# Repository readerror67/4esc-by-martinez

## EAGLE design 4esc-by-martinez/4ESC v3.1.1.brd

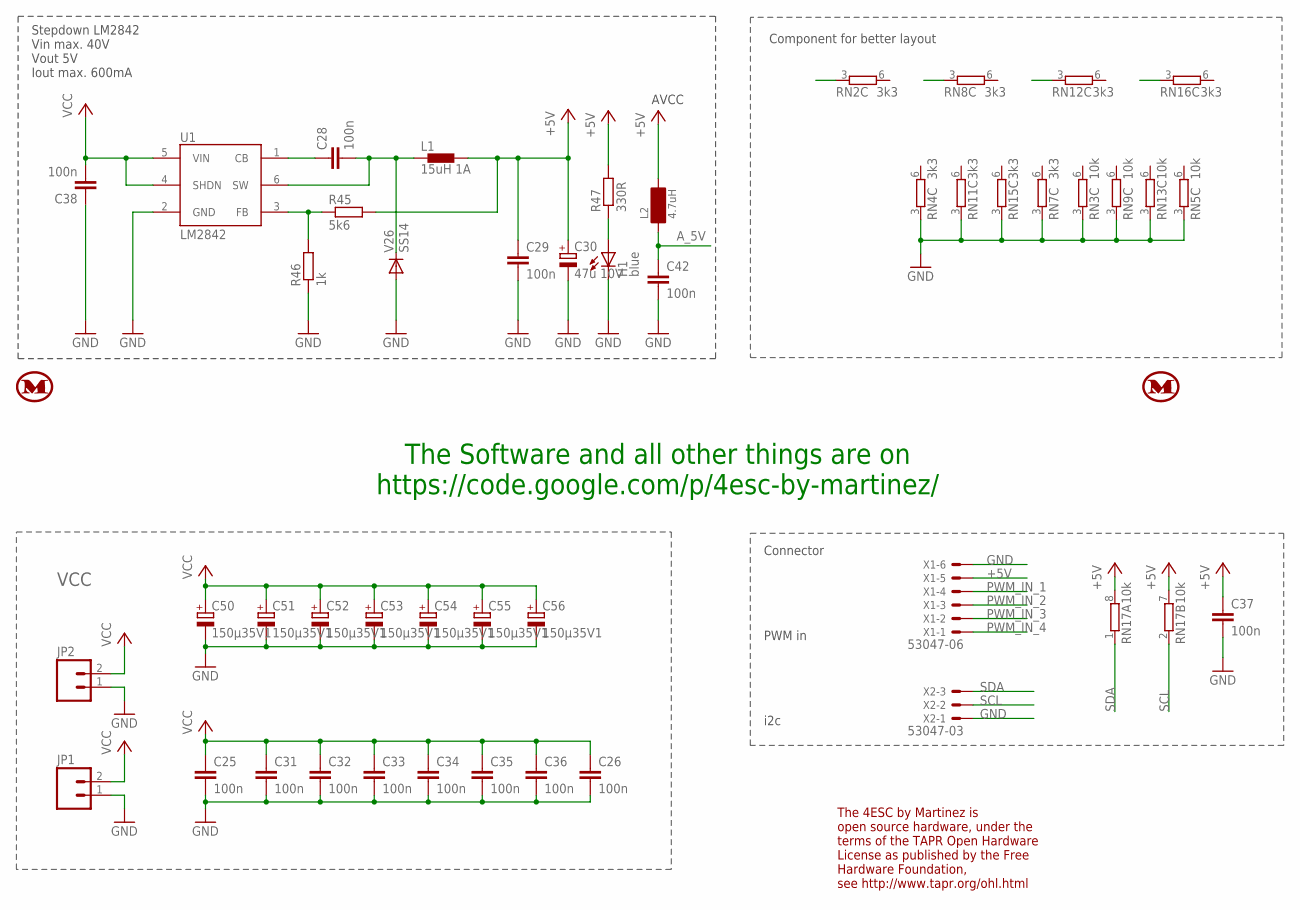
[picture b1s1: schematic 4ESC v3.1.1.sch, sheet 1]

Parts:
C25, C26, C28, C29, C31, C32, C33, C34, C35, C36, C37, C42: 100n; C0603K
C30: 47u 10V; C/6032-28R
C38: 100n; C1206
C50, C51, C52, C53, C54, C55, C56: 150µ35V1; ELKO_MARTINEZ
H1: blue; CHIPLED_0603
JP1, JP2: M021X02_NO_SILK; 1X02_NO_SILK
L1: 15uH 1A; CDRH4D28
L2: 4.7uH; L0805
R45: 5k6; R0603
R46: 1k; R0603
R47: 330R; R0603
RN2, RN4, RN7, RN8, RN11, RN12, RN15, RN16: 3k3; 4X0402ARV341
RN3, RN5, RN9, RN13, RN17: 10k; 4X0402ARV341
U1: LM2842; SOT23-6
U$1, U$2: M
U$3, U$4: 4ESC_05MM; 4ESC_05MM_HOCH
V26: SS14; DO214AC
X1: 53047-06
X2: 53047-03

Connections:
+5V: C29.1, C30.+, C37.1, L1.P$2 (2), L2.2, R45.2, R47.2, RN17.7 (2), RN17.8 (2), X1.5; also elsewhere on the board
A_5V: C42.1, L2.1; also elsewhere on the board
GND: C25.2, C26.2, C29.2, C30.-, C31.2, C32.2, C33.2, C34.2, C35.2, C36.2, C37.2, C38.1, C42.2, C50.-, C50.-1 (-), C51.-, C51.-1 (-), C52.-, C52.-1 (-), C53.-, C53.-1 (-), C54.-, C54.-1 (-), C55.-, C55.-1 (-), C56.-, C56.-1 (-), H1.C, JP1.1, JP2.1, R46.1, RN3.3 (1), RN4.3 (1), RN5.3 (1), RN7.3 (1), RN9.3 (1), RN11.3 (1), RN13.3 (1), RN15.3 (1), U1.2 (GND), V26.A, X1.6, X2.1; also elsewhere on the board
unnamed: C28.2, L1.P$1 (1), U1.6 (SW), V26.C
unnamed: C28.1, U1.1 (CB)
unnamed: R45.1, R46.2, U1.3 (FB)
unnamed: H1.A, R47.1
PWM_IN_1: X1.4; also elsewhere on the board
PWM_IN_2: X1.3; also elsewhere on the board
PWM_IN_3: X1.2; also elsewhere on the board
PWM_IN_4: X1.1; also elsewhere on the board
SCL: RN17.2 (1), X2.2; also elsewhere on the board
SDA: RN17.1, X2.3; also elsewhere on the board
SENSE_STAR_1: RN2.3 (1); also elsewhere on the board
SENSE_STAR_2: RN8.3 (1); also elsewhere on the board
SENSE_STAR_3: RN12.3 (1); also elsewhere on the board
SENSE_STAR_4: RN16.3 (1); also elsewhere on the board
VCC: C25.1, C26.1, C31.1, C32.1, C33.1, C34.1, C35.1, C36.1, C38.2, C50.+, C50.+1 (+), C51.+, C51.+1 (+), C52.+, C52.+1 (+), C53.+, C53.+1 (+), C54.+, C54.+1 (+), C55.+, C55.+1 (+), C56.+, C56.+1 (+), JP1.2, JP2.2, U1.4 (SHDN), U1.5 (VIN); also elsewhere on the board

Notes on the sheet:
VCC
Stepdown LM2842 Vin max. 40V Vout 5V Iout max. 600mA
Connector PWM in i2c
Component for better layout
AVCC
The 4ESC by Martinez is open source hardware, under the terms of the TAPR Open Hardware License as published by the Free Hardware Foundation, see http://www.tapr.org/ohl.html
The Software and all other things are on https://code.google.com/p/4esc-by-martinez/

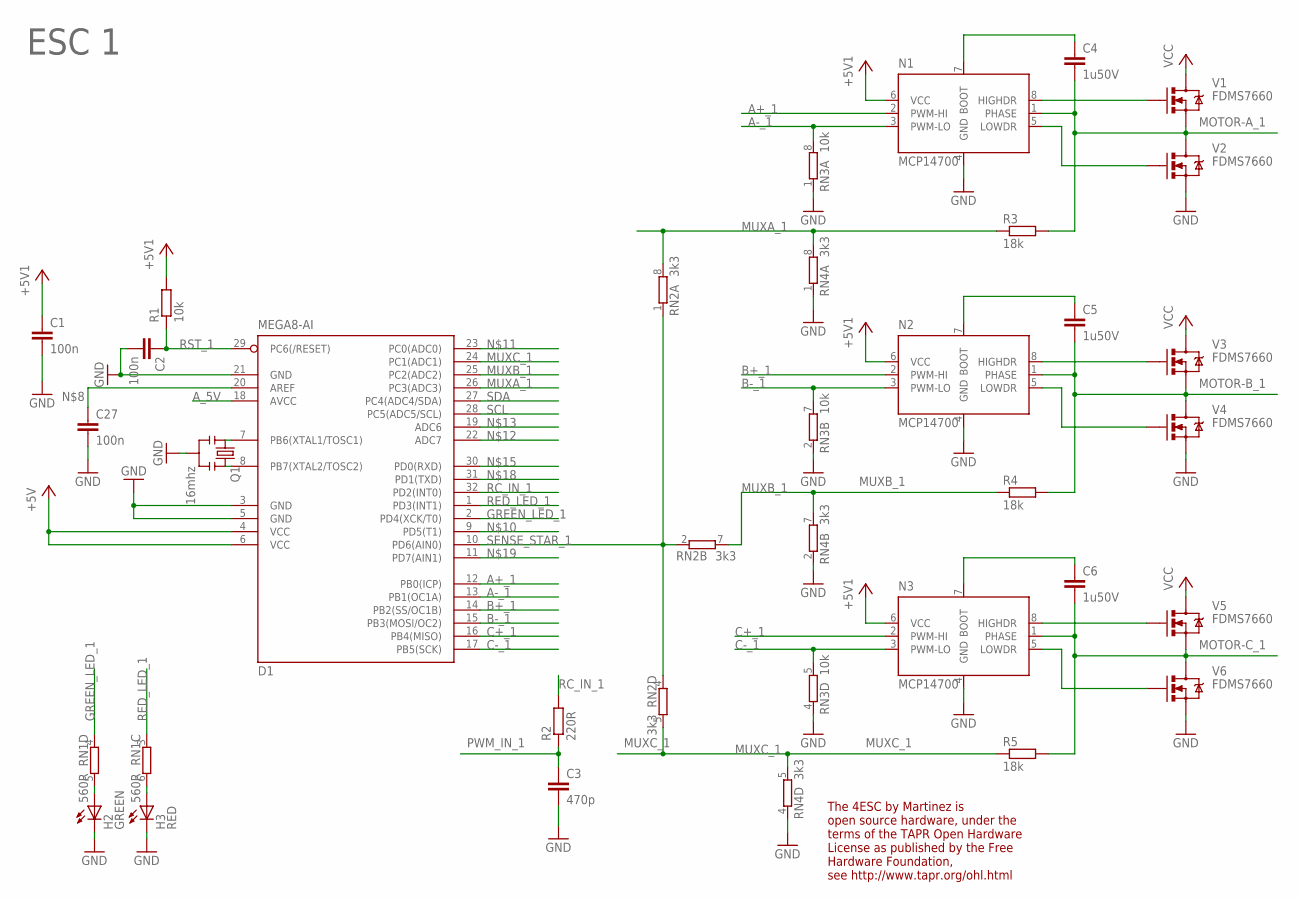
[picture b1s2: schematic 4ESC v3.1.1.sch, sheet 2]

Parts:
C1, C2, C27: 100n; C0603K
C3: 470p; C0603K
C4, C5, C6: 1u50V; C0805K
D1: MEGA8-AI; TQFP32-08
H2: GREEN; CHIPLED_0603
H3: RED; CHIPLED_0603
N1, N2, N3: MCP14700; DFN3X3P8
Q1: 16mhz; RESONATOR-SMD
R1: 10k; R0603
R2: 220R; R0603
R3, R4, R5: 18k; R0603
RN1: 560R; 4X0402ARV341
RN2, RN4: 3k3; 4X0402ARV341
RN3: 10k; 4X0402ARV341
V1, V2, V3, V4, V5, V6: FDMS7660; POWER56

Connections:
+5V: C1.1, D1.4 (VCC), D1.6 (VCC), N1.6 (VCC), N2.6 (VCC), N3.6 (VCC), R1.2; also elsewhere on the board
A+_1: D1.12 (PB0(ICP)), N1.2 (PWM-HI)
A-_1: D1.13 (PB1(OC1A)), N1.3 (PWM-LO), RN3.8 (2)
A_5V: D1.18 (AVCC); also elsewhere on the board
B+_1: D1.14 (PB2(SS/OC1B)), N2.2 (PWM-HI)
B-_1: D1.15 (PB3(MOSI/OC2)), N2.3 (PWM-LO), RN3.7 (2)
C+_1: D1.16 (PB4(MISO)), N3.2 (PWM-HI)
C-_1: D1.17 (PB5(SCK)), N3.3 (PWM-LO), RN3.5 (2)
GND: C1.2, C2.2, C3.2, C27.2, D1.3 (GND), D1.5 (GND), D1.21 (GND), H2.C, H3.C, N1.4 (GND), N2.4 (GND), N3.4 (GND), Q1.2, RN3.1, RN3.2 (1), RN3.4 (1), RN4.1, RN4.2 (1), RN4.4 (1), V2.P$1 (S), V2.P$2 (S), V2.P$3 (S), V4.P$1 (S), V4.P$2 (S), V4.P$3 (S), V6.P$1 (S), V6.P$2 (S), V6.P$3 (S); also elsewhere on the board
GREEN_LED_1: D1.2 (PD4(XCK/T0)), RN1.4 (1)
MOTOR-A_1: C4.2, N1.1 (PHASE), R3.2, V1.P$1 (S), V1.P$2 (S), V1.P$3 (S), V2.P$5 (D), V2.P$6 (D), V2.P$7 (D), V2.P$8 (D), V2.P$9 (D)
MOTOR-B_1: C5.2, N2.1 (PHASE), R4.2, V3.P$1 (S), V3.P$2 (S), V3.P$3 (S), V4.P$5 (D), V4.P$6 (D), V4.P$7 (D), V4.P$8 (D), V4.P$9 (D)
MOTOR-C_1: C6.2, N3.1 (PHASE), R5.2, V5.P$1 (S), V5.P$2 (S), V5.P$3 (S), V6.P$5 (D), V6.P$6 (D), V6.P$7 (D), V6.P$8 (D), V6.P$9 (D)
MUXA_1: D1.26 (PC3(ADC3)), R3.1, RN2.8 (2), RN4.8 (2)
MUXB_1: D1.25 (PC2(ADC2)), R4.1, RN2.7 (2), RN4.7 (2)
MUXC_1: D1.24 (PC1(ADC1)), R5.1, RN2.5 (2), RN4.5 (2)
unnamed: N1.5 (LOWDR), V2.P$4 (G)
unnamed: N2.5 (LOWDR), V4.P$4 (G)
unnamed: D1.8 (PB7(XTAL2/TOSC2)), Q1.3
unnamed: N3.5 (LOWDR), V6.P$4 (G)
unnamed: D1.7 (PB6(XTAL1/TOSC1)), Q1.1
unnamed: H3.A, RN1.6 (2)
unnamed: H2.A, RN1.5 (2)
unnamed: C27.1, D1.20 (AREF)
unnamed: N1.8 (HIGHDR), V1.P$4 (G)
unnamed: N2.8 (HIGHDR), V3.P$4 (G)
unnamed: N3.8 (HIGHDR), V5.P$4 (G)
unnamed: C4.1, N1.7 (BOOT)
unnamed: C5.1, N2.7 (BOOT)
unnamed: C6.1, N3.7 (BOOT)
PWM_IN_1: C3.1, R2.1; also elsewhere on the board
RC_IN_1: D1.32 (PD2(INT0)), R2.2
RED_LED_1: D1.1 (PD3(INT1)), RN1.3 (1)
RST_1: C2.1, D1.29 (PC6(/RESET)), R1.1
SCL: D1.28 (PC5(ADC5/SCL)); also elsewhere on the board
SDA: D1.27 (PC4(ADC4/SDA)); also elsewhere on the board
SENSE_STAR_1: D1.10 (PD6(AIN0)), RN2.1, RN2.2 (1), RN2.4 (1); also elsewhere on the board
VCC: V1.P$5 (D), V1.P$6 (D), V1.P$7 (D), V1.P$8 (D), V1.P$9 (D), V3.P$5 (D), V3.P$6 (D), V3.P$7 (D), V3.P$8 (D), V3.P$9 (D), V5.P$5 (D), V5.P$6 (D), V5.P$7 (D), V5.P$8 (D), V5.P$9 (D); also elsewhere on the board

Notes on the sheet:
ESC 1
The 4ESC by Martinez is open source hardware, under the terms of the TAPR Open Hardware License as published by the Free Hardware Foundation, see http://www.tapr.org/ohl.html

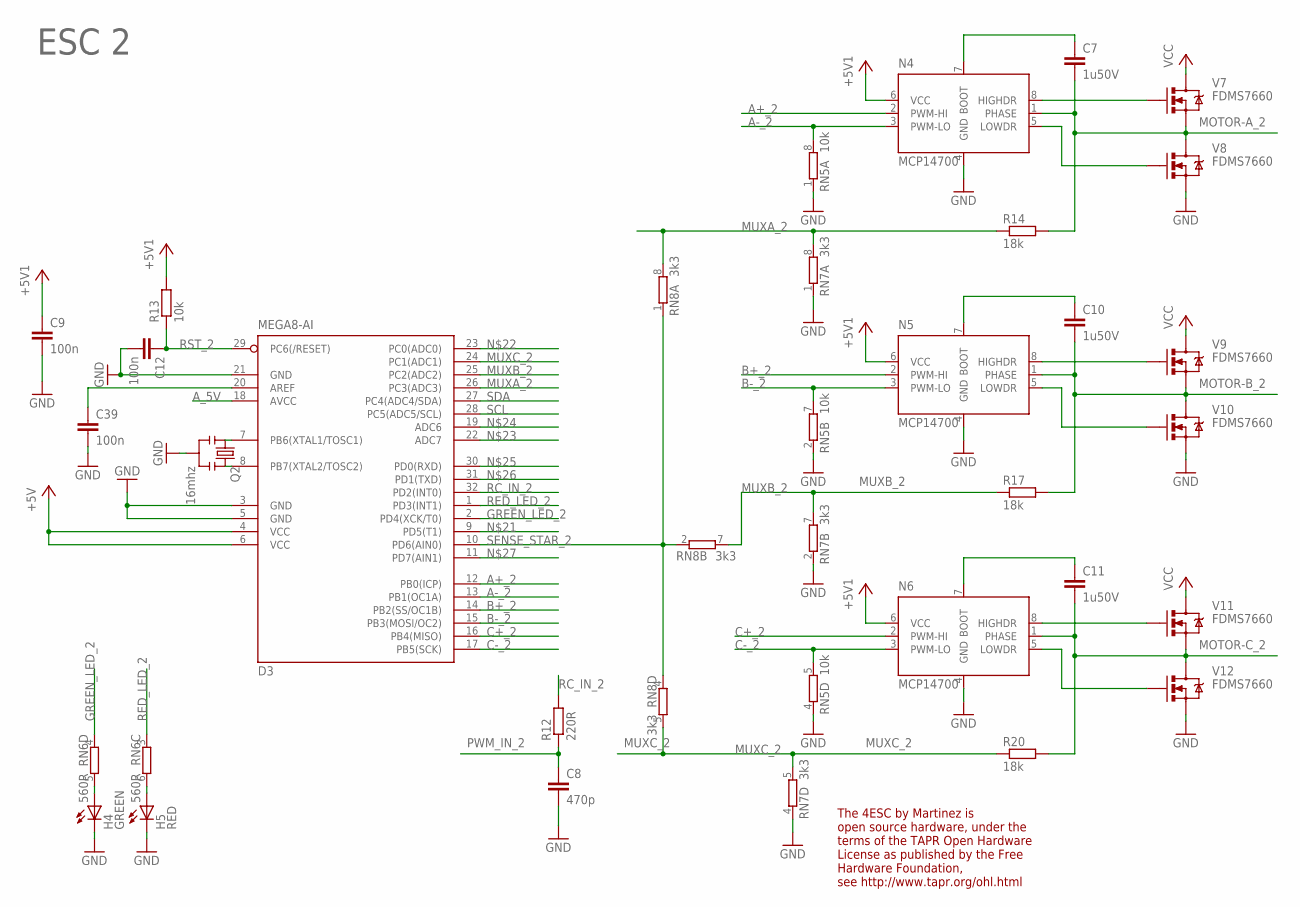
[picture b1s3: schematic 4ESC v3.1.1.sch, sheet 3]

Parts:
C7, C10, C11: 1u50V; C0805K
C8: 470p; C0603K
C9, C12, C39: 100n; C0603K
D3: MEGA8-AI; TQFP32-08
H4: GREEN; CHIPLED_0603
H5: RED; CHIPLED_0603
N4, N5, N6: MCP14700; DFN3X3P8
Q2: 16mhz; RESONATOR-SMD
R12: 220R; R0603
R13: 10k; R0603
R14, R17, R20: 18k; R0603
RN5: 10k; 4X0402ARV341
RN6: 560R; 4X0402ARV341
RN7, RN8: 3k3; 4X0402ARV341
V7, V8, V9, V10, V11, V12: FDMS7660; POWER56

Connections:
+5V: C9.1, D3.4 (VCC), D3.6 (VCC), N4.6 (VCC), N5.6 (VCC), N6.6 (VCC), R13.2; also elsewhere on the board
A+_2: D3.12 (PB0(ICP)), N4.2 (PWM-HI)
A-_2: D3.13 (PB1(OC1A)), N4.3 (PWM-LO), RN5.8 (2)
A_5V: D3.18 (AVCC); also elsewhere on the board
B+_2: D3.14 (PB2(SS/OC1B)), N5.2 (PWM-HI)
B-_2: D3.15 (PB3(MOSI/OC2)), N5.3 (PWM-LO), RN5.7 (2)
C+_2: D3.16 (PB4(MISO)), N6.2 (PWM-HI)
C-_2: D3.17 (PB5(SCK)), N6.3 (PWM-LO), RN5.5 (2)
GND: C8.2, C9.2, C12.2, C39.2, D3.3 (GND), D3.5 (GND), D3.21 (GND), H4.C, H5.C, N4.4 (GND), N5.4 (GND), N6.4 (GND), Q2.2, RN5.1, RN5.2 (1), RN5.4 (1), RN7.1, RN7.2 (1), RN7.4 (1), V8.P$1 (S), V8.P$2 (S), V8.P$3 (S), V10.P$1 (S), V10.P$2 (S), V10.P$3 (S), V12.P$1 (S), V12.P$2 (S), V12.P$3 (S); also elsewhere on the board
GREEN_LED_2: D3.2 (PD4(XCK/T0)), RN6.4 (1)
MOTOR-A_2: C7.2, N4.1 (PHASE), R14.2, V7.P$1 (S), V7.P$2 (S), V7.P$3 (S), V8.P$5 (D), V8.P$6 (D), V8.P$7 (D), V8.P$8 (D), V8.P$9 (D)
MOTOR-B_2: C10.2, N5.1 (PHASE), R17.2, V9.P$1 (S), V9.P$2 (S), V9.P$3 (S), V10.P$5 (D), V10.P$6 (D), V10.P$7 (D), V10.P$8 (D), V10.P$9 (D)
MOTOR-C_2: C11.2, N6.1 (PHASE), R20.2, V11.P$1 (S), V11.P$2 (S), V11.P$3 (S), V12.P$5 (D), V12.P$6 (D), V12.P$7 (D), V12.P$8 (D), V12.P$9 (D)
MUXA_2: D3.26 (PC3(ADC3)), R14.1, RN7.8 (2), RN8.8 (2)
MUXB_2: D3.25 (PC2(ADC2)), R17.1, RN7.7 (2), RN8.7 (2)
MUXC_2: D3.24 (PC1(ADC1)), R20.1, RN7.5 (2), RN8.5 (2)
unnamed: D3.8 (PB7(XTAL2/TOSC2)), Q2.3
unnamed: D3.7 (PB6(XTAL1/TOSC1)), Q2.1
unnamed: N4.5 (LOWDR), V8.P$4 (G)
unnamed: N5.5 (LOWDR), V10.P$4 (G)
unnamed: N6.5 (LOWDR), V12.P$4 (G)
unnamed: H4.A, RN6.5 (2)
unnamed: N4.8 (HIGHDR), V7.P$4 (G)
unnamed: N5.8 (HIGHDR), V9.P$4 (G)
unnamed: N6.8 (HIGHDR), V11.P$4 (G)
unnamed: C39.1, D3.20 (AREF)
unnamed: H5.A, RN6.6 (2)
unnamed: C7.1, N4.7 (BOOT)
unnamed: C10.1, N5.7 (BOOT)
unnamed: C11.1, N6.7 (BOOT)
PWM_IN_2: C8.1, R12.1; also elsewhere on the board
RC_IN_2: D3.32 (PD2(INT0)), R12.2
RED_LED_2: D3.1 (PD3(INT1)), RN6.3 (1)
RST_2: C12.1, D3.29 (PC6(/RESET)), R13.1
SCL: D3.28 (PC5(ADC5/SCL)); also elsewhere on the board
SDA: D3.27 (PC4(ADC4/SDA)); also elsewhere on the board
SENSE_STAR_2: D3.10 (PD6(AIN0)), RN8.1, RN8.2 (1), RN8.4 (1); also elsewhere on the board
VCC: V7.P$5 (D), V7.P$6 (D), V7.P$7 (D), V7.P$8 (D), V7.P$9 (D), V9.P$5 (D), V9.P$6 (D), V9.P$7 (D), V9.P$8 (D), V9.P$9 (D), V11.P$5 (D), V11.P$6 (D), V11.P$7 (D), V11.P$8 (D), V11.P$9 (D); also elsewhere on the board

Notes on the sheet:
ESC 2
The 4ESC by Martinez is open source hardware, under the terms of the TAPR Open Hardware License as published by the Free Hardware Foundation, see http://www.tapr.org/ohl.html

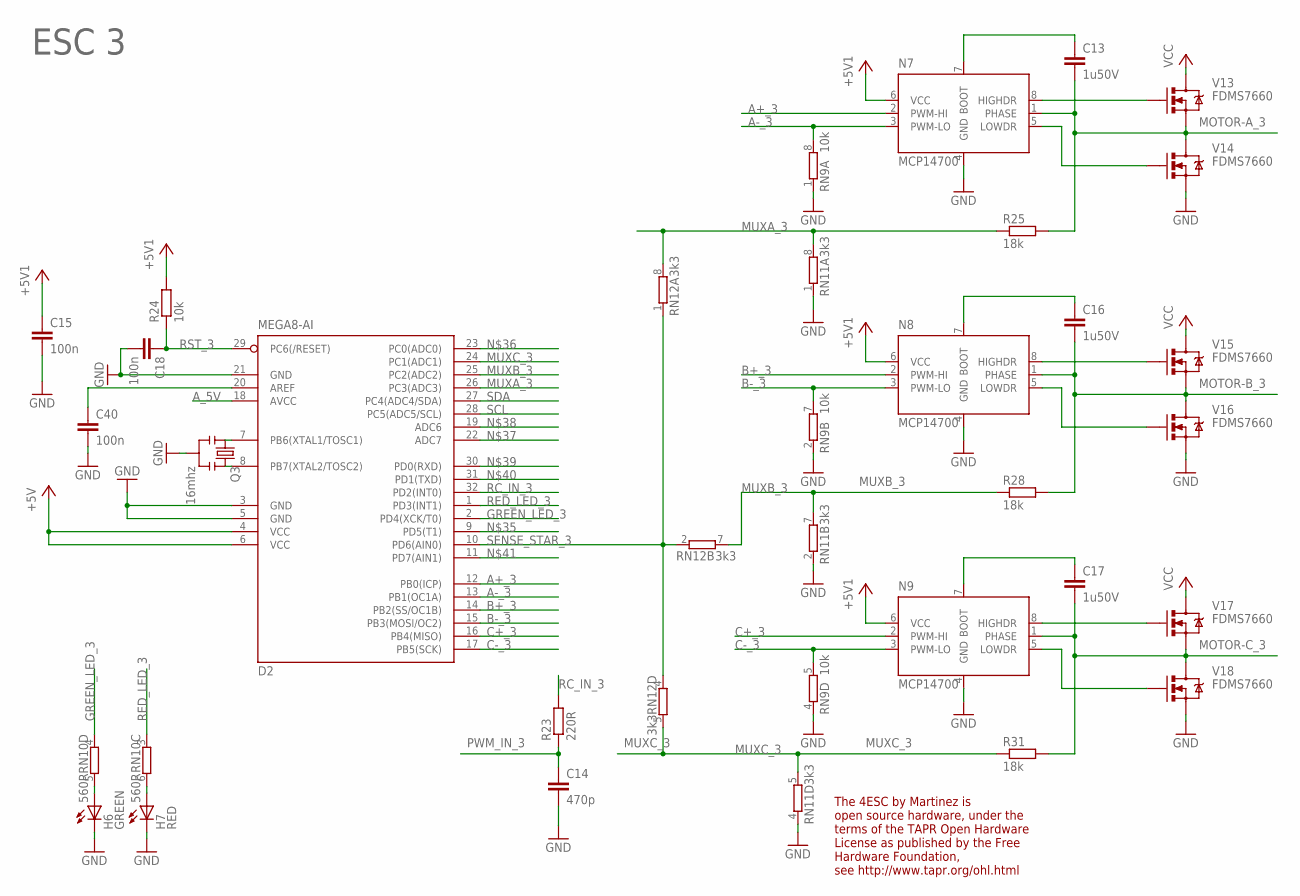
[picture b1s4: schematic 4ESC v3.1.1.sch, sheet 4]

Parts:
C13, C16, C17: 1u50V; C0805K
C14: 470p; C0603K
C15, C18, C40: 100n; C0603K
D2: MEGA8-AI; TQFP32-08
H6: GREEN; CHIPLED_0603
H7: RED; CHIPLED_0603
N7, N8, N9: MCP14700; DFN3X3P8
Q3: 16mhz; RESONATOR-SMD
R23: 220R; R0603
R24: 10k; R0603
R25, R28, R31: 18k; R0603
RN9: 10k; 4X0402ARV341
RN10: 560R; 4X0402ARV341
RN11, RN12: 3k3; 4X0402ARV341
V13, V14, V15, V16, V17, V18: FDMS7660; POWER56

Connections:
+5V: C15.1, D2.4 (VCC), D2.6 (VCC), N7.6 (VCC), N8.6 (VCC), N9.6 (VCC), R24.2; also elsewhere on the board
A+_3: D2.12 (PB0(ICP)), N7.2 (PWM-HI)
A-_3: D2.13 (PB1(OC1A)), N7.3 (PWM-LO), RN9.8 (2)
A_5V: D2.18 (AVCC); also elsewhere on the board
B+_3: D2.14 (PB2(SS/OC1B)), N8.2 (PWM-HI)
B-_3: D2.15 (PB3(MOSI/OC2)), N8.3 (PWM-LO), RN9.7 (2)
C+_3: D2.16 (PB4(MISO)), N9.2 (PWM-HI)
C-_3: D2.17 (PB5(SCK)), N9.3 (PWM-LO), RN9.5 (2)
GND: C14.2, C15.2, C18.2, C40.2, D2.3 (GND), D2.5 (GND), D2.21 (GND), H6.C, H7.C, N7.4 (GND), N8.4 (GND), N9.4 (GND), Q3.2, RN9.1, RN9.2 (1), RN9.4 (1), RN11.1, RN11.2 (1), RN11.4 (1), V14.P$1 (S), V14.P$2 (S), V14.P$3 (S), V16.P$1 (S), V16.P$2 (S), V16.P$3 (S), V18.P$1 (S), V18.P$2 (S), V18.P$3 (S); also elsewhere on the board
GREEN_LED_3: D2.2 (PD4(XCK/T0)), RN10.4 (1)
MOTOR-A_3: C13.2, N7.1 (PHASE), R25.2, V13.P$1 (S), V13.P$2 (S), V13.P$3 (S), V14.P$5 (D), V14.P$6 (D), V14.P$7 (D), V14.P$8 (D), V14.P$9 (D)
MOTOR-B_3: C16.2, N8.1 (PHASE), R28.2, V15.P$1 (S), V15.P$2 (S), V15.P$3 (S), V16.P$5 (D), V16.P$6 (D), V16.P$7 (D), V16.P$8 (D), V16.P$9 (D)
MOTOR-C_3: C17.2, N9.1 (PHASE), R31.2, V17.P$1 (S), V17.P$2 (S), V17.P$3 (S), V18.P$5 (D), V18.P$6 (D), V18.P$7 (D), V18.P$8 (D), V18.P$9 (D)
MUXA_3: D2.26 (PC3(ADC3)), R25.1, RN11.8 (2), RN12.8 (2)
MUXB_3: D2.25 (PC2(ADC2)), R28.1, RN11.7 (2), RN12.7 (2)
MUXC_3: D2.24 (PC1(ADC1)), R31.1, RN11.5 (2), RN12.5 (2)
unnamed: D2.8 (PB7(XTAL2/TOSC2)), Q3.3
unnamed: D2.7 (PB6(XTAL1/TOSC1)), Q3.1
unnamed: C40.1, D2.20 (AREF)
unnamed: N7.8 (HIGHDR), V13.P$4 (G)
unnamed: N8.8 (HIGHDR), V15.P$4 (G)
unnamed: N9.8 (HIGHDR), V17.P$4 (G)
unnamed: N7.5 (LOWDR), V14.P$4 (G)
unnamed: N8.5 (LOWDR), V16.P$4 (G)
unnamed: N9.5 (LOWDR), V18.P$4 (G)
unnamed: H6.A, RN10.5 (2)
unnamed: H7.A, RN10.6 (2)
unnamed: C13.1, N7.7 (BOOT)
unnamed: C16.1, N8.7 (BOOT)
unnamed: C17.1, N9.7 (BOOT)
PWM_IN_3: C14.1, R23.1; also elsewhere on the board
RC_IN_3: D2.32 (PD2(INT0)), R23.2
RED_LED_3: D2.1 (PD3(INT1)), RN10.3 (1)
RST_3: C18.1, D2.29 (PC6(/RESET)), R24.1
SCL: D2.28 (PC5(ADC5/SCL)); also elsewhere on the board
SDA: D2.27 (PC4(ADC4/SDA)); also elsewhere on the board
SENSE_STAR_3: D2.10 (PD6(AIN0)), RN12.1, RN12.2 (1), RN12.4 (1); also elsewhere on the board
VCC: V13.P$5 (D), V13.P$6 (D), V13.P$7 (D), V13.P$8 (D), V13.P$9 (D), V15.P$5 (D), V15.P$6 (D), V15.P$7 (D), V15.P$8 (D), V15.P$9 (D), V17.P$5 (D), V17.P$6 (D), V17.P$7 (D), V17.P$8 (D), V17.P$9 (D); also elsewhere on the board

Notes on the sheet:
ESC 3
The 4ESC by Martinez is open source hardware, under the terms of the TAPR Open Hardware License as published by the Free Hardware Foundation, see http://www.tapr.org/ohl.html

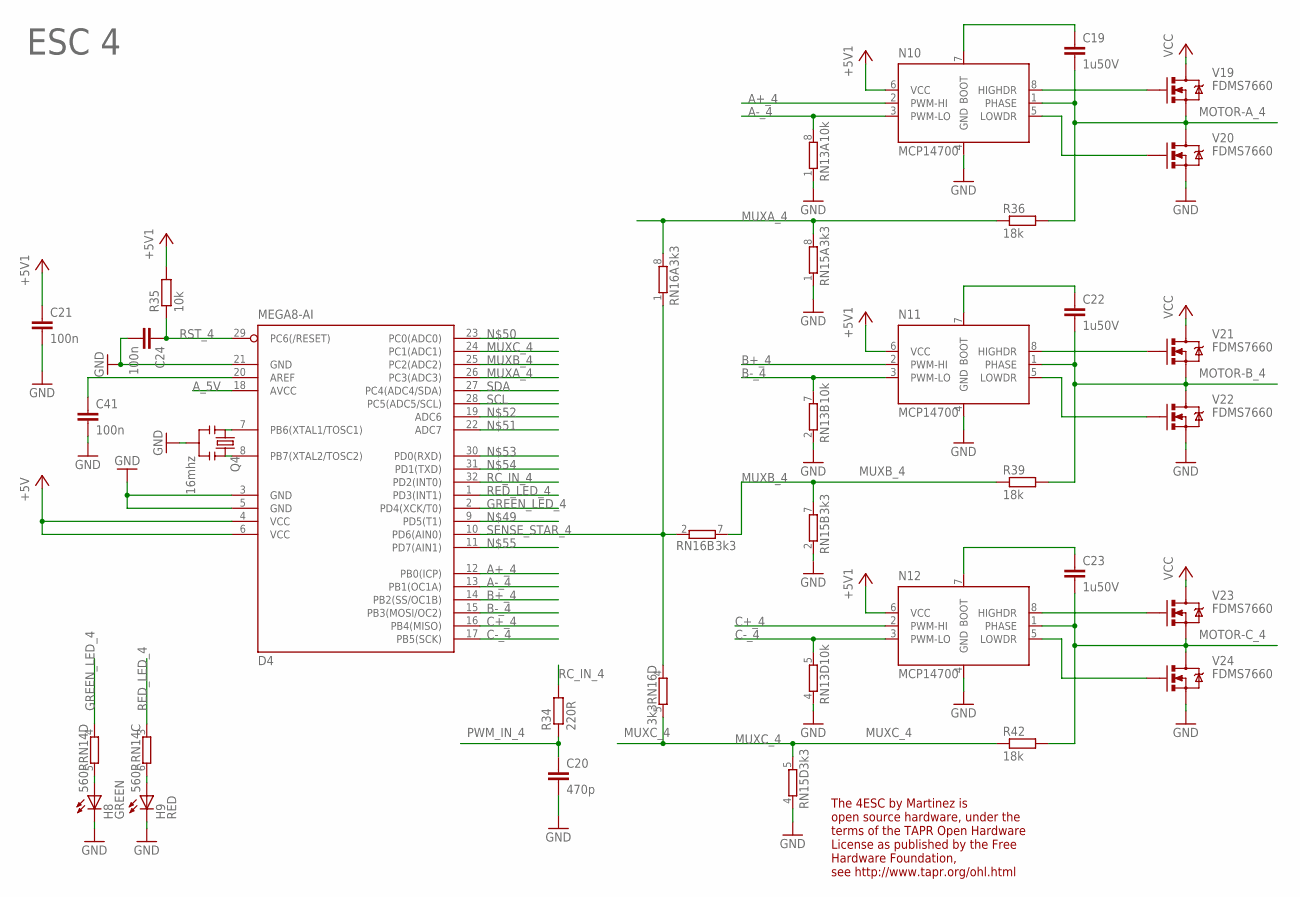
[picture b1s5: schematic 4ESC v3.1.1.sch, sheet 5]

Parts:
C19, C22, C23: 1u50V; C0805K
C20: 470p; C0603K
C21, C24, C41: 100n; C0603K
D4: MEGA8-AI; TQFP32-08
H8: GREEN; CHIPLED_0603
H9: RED; CHIPLED_0603
N10, N11, N12: MCP14700; DFN3X3P8
Q4: 16mhz; RESONATOR-SMD
R34: 220R; R0603
R35: 10k; R0603
R36, R39, R42: 18k; R0603
RN13: 10k; 4X0402ARV341
RN14: 560R; 4X0402ARV341
RN15, RN16: 3k3; 4X0402ARV341
V19, V20, V21, V22, V23, V24: FDMS7660; POWER56

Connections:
+5V: C21.1, D4.4 (VCC), D4.6 (VCC), N10.6 (VCC), N11.6 (VCC), N12.6 (VCC), R35.2; also elsewhere on the board
A+_4: D4.12 (PB0(ICP)), N10.2 (PWM-HI)
A-_4: D4.13 (PB1(OC1A)), N10.3 (PWM-LO), RN13.8 (2)
A_5V: D4.18 (AVCC); also elsewhere on the board
B+_4: D4.14 (PB2(SS/OC1B)), N11.2 (PWM-HI)
B-_4: D4.15 (PB3(MOSI/OC2)), N11.3 (PWM-LO), RN13.7 (2)
C+_4: D4.16 (PB4(MISO)), N12.2 (PWM-HI)
C-_4: D4.17 (PB5(SCK)), N12.3 (PWM-LO), RN13.5 (2)
GND: C20.2, C21.2, C24.2, C41.2, D4.3 (GND), D4.5 (GND), D4.21 (GND), H8.C, H9.C, N10.4 (GND), N11.4 (GND), N12.4 (GND), Q4.2, RN13.1, RN13.2 (1), RN13.4 (1), RN15.1, RN15.2 (1), RN15.4 (1), V20.P$1 (S), V20.P$2 (S), V20.P$3 (S), V22.P$1 (S), V22.P$2 (S), V22.P$3 (S), V24.P$1 (S), V24.P$2 (S), V24.P$3 (S); also elsewhere on the board
GREEN_LED_4: D4.2 (PD4(XCK/T0)), RN14.4 (1)
MOTOR-A_4: C19.2, N10.1 (PHASE), R36.2, V19.P$1 (S), V19.P$2 (S), V19.P$3 (S), V20.P$5 (D), V20.P$6 (D), V20.P$7 (D), V20.P$8 (D), V20.P$9 (D)
MOTOR-B_4: C22.2, N11.1 (PHASE), R39.2, V21.P$1 (S), V21.P$2 (S), V21.P$3 (S), V22.P$5 (D), V22.P$6 (D), V22.P$7 (D), V22.P$8 (D), V22.P$9 (D)
MOTOR-C_4: C23.2, N12.1 (PHASE), R42.2, V23.P$1 (S), V23.P$2 (S), V23.P$3 (S), V24.P$5 (D), V24.P$6 (D), V24.P$7 (D), V24.P$8 (D), V24.P$9 (D)
MUXA_4: D4.26 (PC3(ADC3)), R36.1, RN15.8 (2), RN16.8 (2)
MUXB_4: D4.25 (PC2(ADC2)), R39.1, RN15.7 (2), RN16.7 (2)
MUXC_4: D4.24 (PC1(ADC1)), R42.1, RN15.5 (2), RN16.5 (2)
unnamed: D4.8 (PB7(XTAL2/TOSC2)), Q4.3
unnamed: D4.7 (PB6(XTAL1/TOSC1)), Q4.1
unnamed: N10.8 (HIGHDR), V19.P$4 (G)
unnamed: N11.8 (HIGHDR), V21.P$4 (G)
unnamed: N12.8 (HIGHDR), V23.P$4 (G)
unnamed: C41.1, D4.20 (AREF)
unnamed: N10.5 (LOWDR), V20.P$4 (G)
unnamed: N11.5 (LOWDR), V22.P$4 (G)
unnamed: N12.5 (LOWDR), V24.P$4 (G)
unnamed: H8.A, RN14.5 (2)
unnamed: H9.A, RN14.6 (2)
unnamed: C19.1, N10.7 (BOOT)
unnamed: C22.1, N11.7 (BOOT)
unnamed: C23.1, N12.7 (BOOT)
PWM_IN_4: C20.1, R34.1; also elsewhere on the board
RC_IN_4: D4.32 (PD2(INT0)), R34.2
RED_LED_4: D4.1 (PD3(INT1)), RN14.3 (1)
RST_4: C24.1, D4.29 (PC6(/RESET)), R35.1
SCL: D4.28 (PC5(ADC5/SCL)); also elsewhere on the board
SDA: D4.27 (PC4(ADC4/SDA)); also elsewhere on the board
SENSE_STAR_4: D4.10 (PD6(AIN0)), RN16.1, RN16.2 (1), RN16.4 (1); also elsewhere on the board
VCC: V19.P$5 (D), V19.P$6 (D), V19.P$7 (D), V19.P$8 (D), V19.P$9 (D), V21.P$5 (D), V21.P$6 (D), V21.P$7 (D), V21.P$8 (D), V21.P$9 (D), V23.P$5 (D), V23.P$6 (D), V23.P$7 (D), V23.P$8 (D), V23.P$9 (D); also elsewhere on the board

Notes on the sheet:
ESC 4
The 4ESC by Martinez is open source hardware, under the terms of the TAPR Open Hardware License as published by the Free Hardware Foundation, see http://www.tapr.org/ohl.html

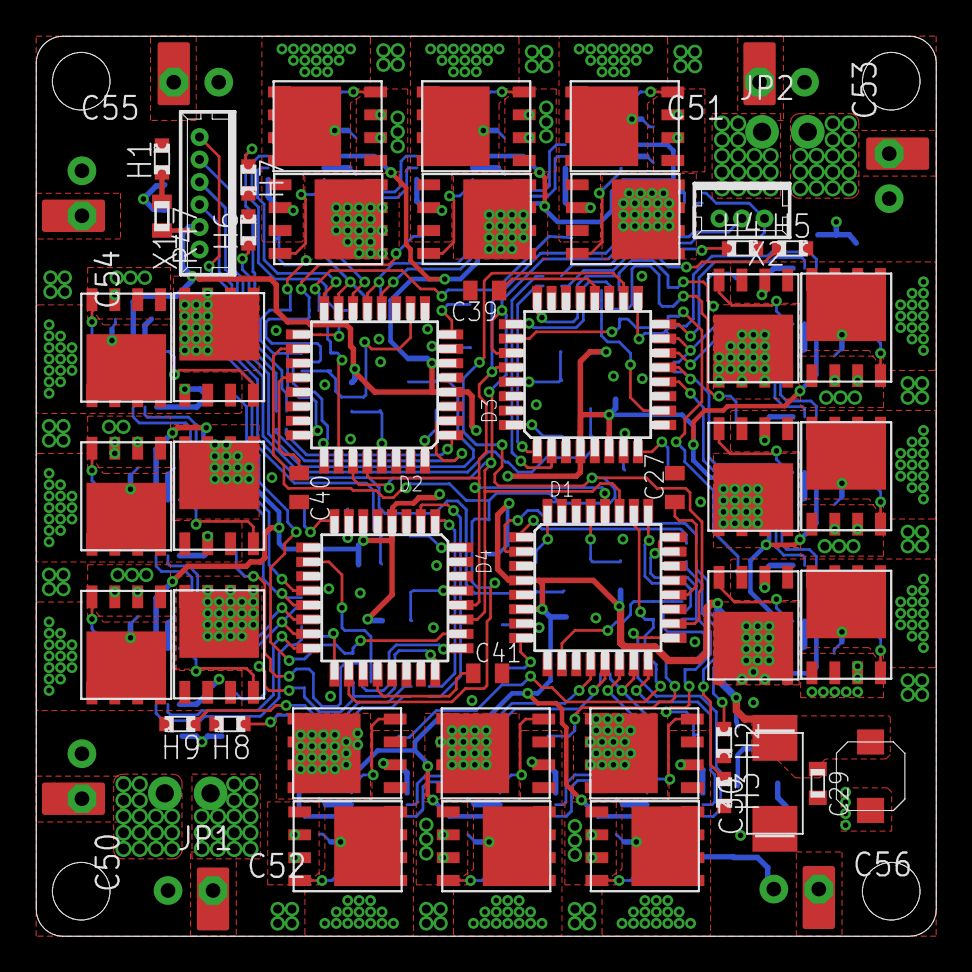
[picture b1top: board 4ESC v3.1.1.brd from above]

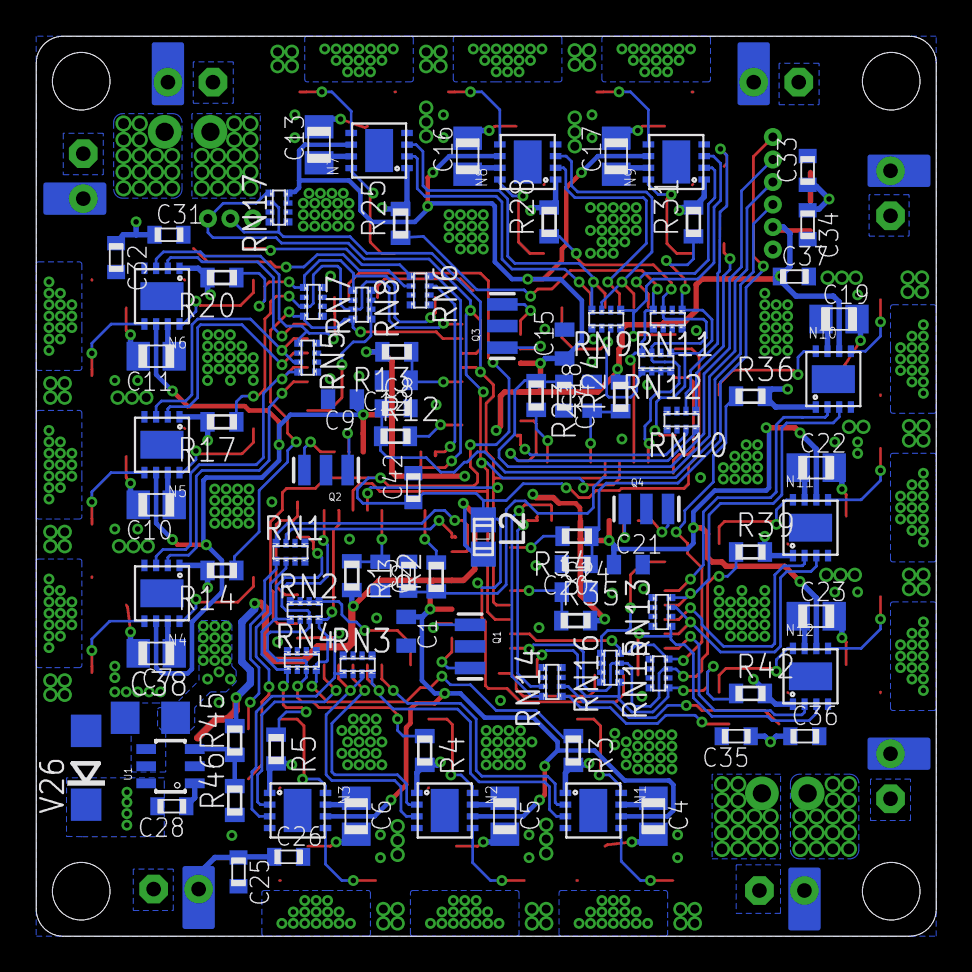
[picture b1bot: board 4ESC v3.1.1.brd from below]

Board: 4 copper layers, 50.0 x 50.0 mm, 154 parts (96 on the bottom side), 138 nets.

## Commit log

2013-11-15 initial
2013-11-15 Typo
2013-11-16 neue Version SimonK
2013-11-16 zusätzliche MOTOR_ADVANCE und TIMING_OFFSET eingefügt
2013-11-16 COMP_PWM .if und #if martinezV3 fuer avra eingefuegt
2013-11-16 nur noch ein .inc File
2013-11-16 auf ein inc geaendert
2013-11-16 Kommentare fuer lazyzero hinzugefuegt
2013-11-17 Tabulator error removed
2013-11-19 intial
2013-11-23 test
2013-11-23 Schrift 4ESC verschoben
2013-11-23 DESCRIPTION changed
2013-11-23 remove MartinezV3flasherMAC.py in Utilities
2013-11-23 Utilities/MartinezV3flasherMAC.py deleted
2013-12-18 Layout optimiert
2015-04-01 Migrating wiki contents from Google Code
